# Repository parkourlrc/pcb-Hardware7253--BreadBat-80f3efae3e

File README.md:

# BreadBat
A breadboard power supply that can operate from USB power or battery power with a
selectable output voltage of 3.3V or 5V.
The device also includes a 1.5A battery charger and battery fuel gauge.

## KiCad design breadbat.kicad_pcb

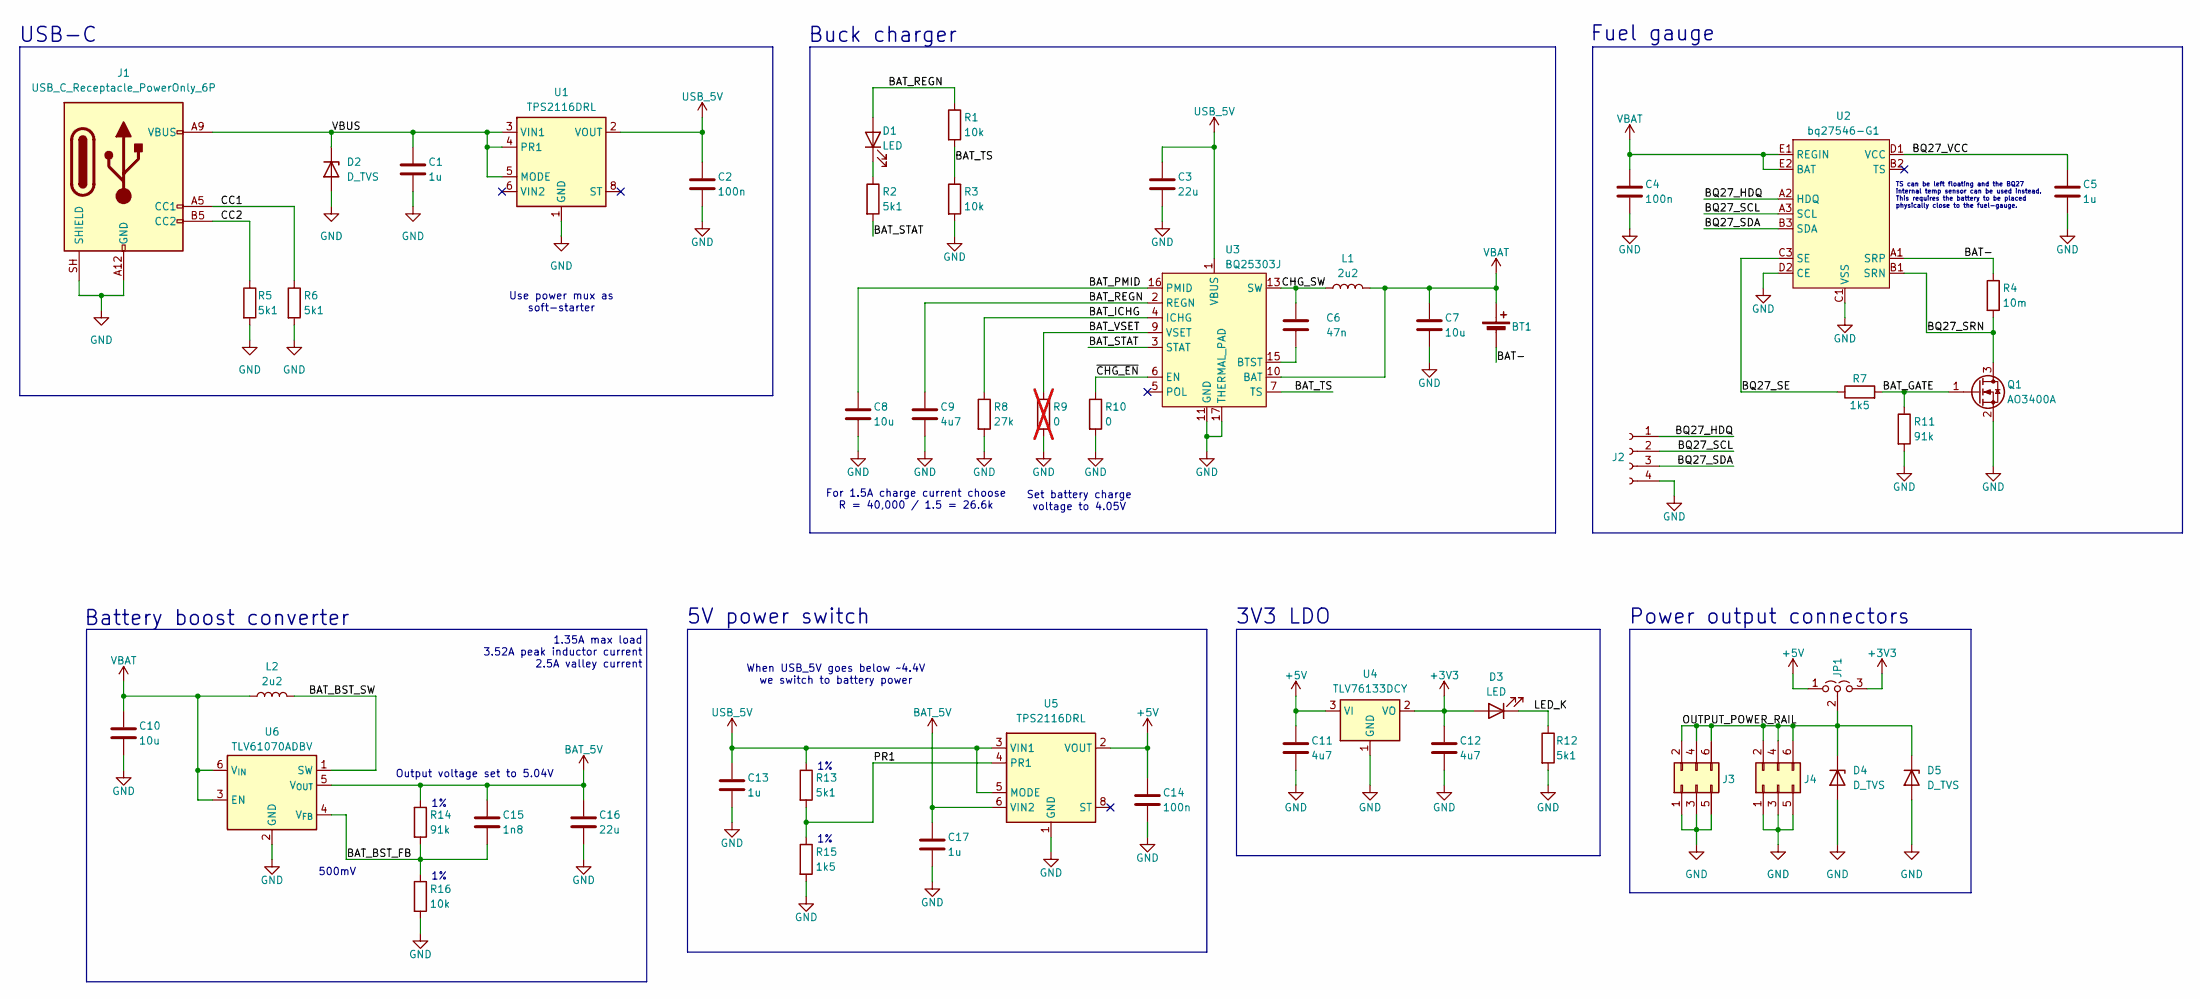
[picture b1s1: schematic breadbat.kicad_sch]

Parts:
BT1: Battery_Cell; JST_PH_B2B-PH-K_1x02_P2.00mm_Vertical_Pin_Swap
C1, C5, C13, C17: 1u; C_0402_1005Metric; LCSC part C29266
C2, C4, C14: 100n; C_0402_1005Metric; LCSC part C1525
C3, C16: 22u; C_0603_1608Metric; LCSC part C7432770
C6: 47n; C_0402_1005Metric; LCSC part C1622
C7, C8, C10: 10u; C_0603_1608Metric; LCSC part C962136
C9, C11, C12: 4u7; C_0603_1608Metric; LCSC part C1705
C15: 1n8; C_0402_1005Metric; LCSC part C107024
D1, D3: LED; LED_0603_1608Metric; LCSC part C2286
D2, D4, D5: D_TVS; D_SOD-323_HandSoldering; Part Number WPE0731D3; LCSC part C5143684
J1: USB_C_Receptacle_PowerOnly_6P; USB_C_Receptacle_HRO_TYPE-C-31-M-17; Part Number YTC-TC6S-231; LCSC part C2927302
J2: Conn_01x04_Socket; PinHeader_1x04_P2.54mm_Vertical
J3, J4: Conn_02x03_Odd_Even; PinHeader_2x03_P2.54mm_Vertical; Part Number PZ254V-12-6P; LCSC part C492420
JP1: Jumper_3_Open; PinHeader_1x03_P2.54mm_Vertical
L1, L2: 2u2; SMD,4.8x4.2mm; LCSC part C54431770
Q1: AO3400A; SOT-23; LCSC part C347475
R1, R3, R16: 10k; R_0402_1005Metric; LCSC part C25744
R2, R12, R13: 5k1; R_0402_1005Metric; LCSC part C25905
R4: 10m; R_1206_3216Metric; LCSC part C46961737
R5, R6: 5k1; R_0402_1005Metric; Part Number 0603WAF5101T5E; LCSC part C25905
R7, R15: 1k5; R_0402_1005Metric; LCSC part C25867
R8: 27k; R_0402_1005Metric; LCSC part C2933084
R9: 0; R_0402_1005Metric; LCSC part C106231; not fitted
R10: 0; R_0402_1005Metric; LCSC part C106231
R11, R14: 91k; R_0402_1005Metric; LCSC part C2909393
U1, U5: TPS2116DRL; SOT-583-8; LCSC part C3235557
U2: bq27546-G1; Texas_DSBGA-15_2.61x1.96mm_Layout5x3_P0.5mm; LCSC part C528629
U3: BQ25303J; WQFN-16-1EP_3x3mm_P0.5mm_EP1.68x1.68mm; LCSC part C2842775
U4: TLV76133DCY; SOT-223-3_TabPin2; LCSC part C7527500
U6: TLV61070ADBV; SOT-23-6; LCSC part C6881375

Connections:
+3V3: C12.1, D3.2 (A), JP1.3 (B), U4.2 (VO)
+5V: C11.1, C14.1, JP1.1 (A), U4.3 (VI), U5.2 (VOUT), U5.7 (VOUT)
/BAT-: BT1.2 (-), R4.1, U2.A1 (SRP)
/BAT_BST_FB: C15.2, R14.2, R16.1, U6.4 (V_{FB})
/BAT_BST_SW: L2.2, U6.1 (SW)
/BAT_GATE: Q1.1 (G), R7.2, R11.1
/BAT_ICHG: R8.1, U3.4 (ICHG)
/BAT_PMID: C8.1, U3.16 (PMID)
/BAT_REGN: C9.1, D1.2 (A), R1.1, U3.2 (REGN)
/BAT_STAT: R2.2, U3.3 (STAT)
/BAT_TS: R1.2, R3.1, U3.7 (TS)
/BAT_VSET: R9.1, U3.9 (VSET)
/BQ27_HDQ: J2.1, U2.A2 (HDQ)
/BQ27_SCL: J2.2, U2.A3 (SCL)
/BQ27_SDA: J2.3, U2.B3 (SDA)
/BQ27_SE: R7.1, U2.C3 (SE)
/BQ27_SRN: Q1.3 (D), R4.2, U2.B1 (SRN)
/BQ27_VCC: C5.1, U2.D1 (VCC)
/CC1: J1.A5 (CC1), R6.1
/CC2: J1.B5 (CC2), R5.1
/CHG_SW: C6.1, L1.1, U3.13 (SW), U3.14 (SW)
/LED_K: D3.1 (K), R12.1
/OUTPUT_POWER_RAIL: D4.1 (K), D5.1 (K), J3.2, J3.4, J3.6, J4.2, J4.4, J4.6, JP1.2 (C)
/PR1: R13.2, R15.1, U5.4 (PR1)
/VBUS: C1.1, D2.1 (K), J1.A9 (VBUS), J1.B9 (VBUS), U1.3 (VIN1), U1.4 (PR1), U1.5 (MODE)
/~CHG_EN: R10.1, U3.6 (EN)
BAT_5V: C15.1, C16.1, C17.1, R14.1, U5.6 (VIN2), U6.5 (V_{OUT})
GND: C1.2, C2.2, C3.2, C4.2, C5.2, C7.2, C8.2, C9.2, C10.2, C11.2, C12.2, C13.2, C14.2, C16.2, C17.2, D2.2 (A), D4.2 (A), D5.2 (A), J1.A12 (GND), J1.B12 (GND), J1.SH (SHIELD), J2.4, J3.1, J3.3, J3.5, J4.1, J4.3, J4.5, Q1.2 (S), R3.2, R5.2, R6.2, R8.2, R9.2, R10.2, R11.2, R12.2, R15.2, R16.2, U1.1 (GND), U2.C1 (VSS), U2.C2 (VSS), U2.D2 (CE), U3.11 (GND), U3.12 (GND), U3.17 (THERMAL_PAD), U4.1 (GND), U5.1 (GND), U6.2 (GND)
unnamed: D1.1 (K), R2.1
unnamed: C6.2, U3.15 (BTST)
USB_5V: C2.1, C3.1, C13.1, R13.1, U1.2 (VOUT), U1.7 (VOUT), U3.1 (VBUS), U5.3 (VIN1), U5.5 (MODE)
VBAT: BT1.1 (+), C4.1, C7.1, C10.1, L1.2, L2.1, U2.E1 (REGIN), U2.E2 (BAT), U3.10 (BAT), U6.3 (EN), U6.6 (V_{IN})

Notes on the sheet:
Power output connectors
For 1.5A charge current choose R = 40,000 / 1.5 = 26.6k
1.35A max load 3.52A peak inductor current 2.5A valley current
Fuel gauge
500mV
TS can be left floating and the BQ27 internal temp sensor can be used instead. This requires the battery to be placed physically close to the fuel-gauge.
Buck charger
Battery boost converter
Output voltage set to 5.04V
When USB_5V goes below ~4.4V we switch to battery power
Set battery charge voltage to 4.05V
Use power mux as soft-starter
3V3 LDO
5V power switch
USB-C

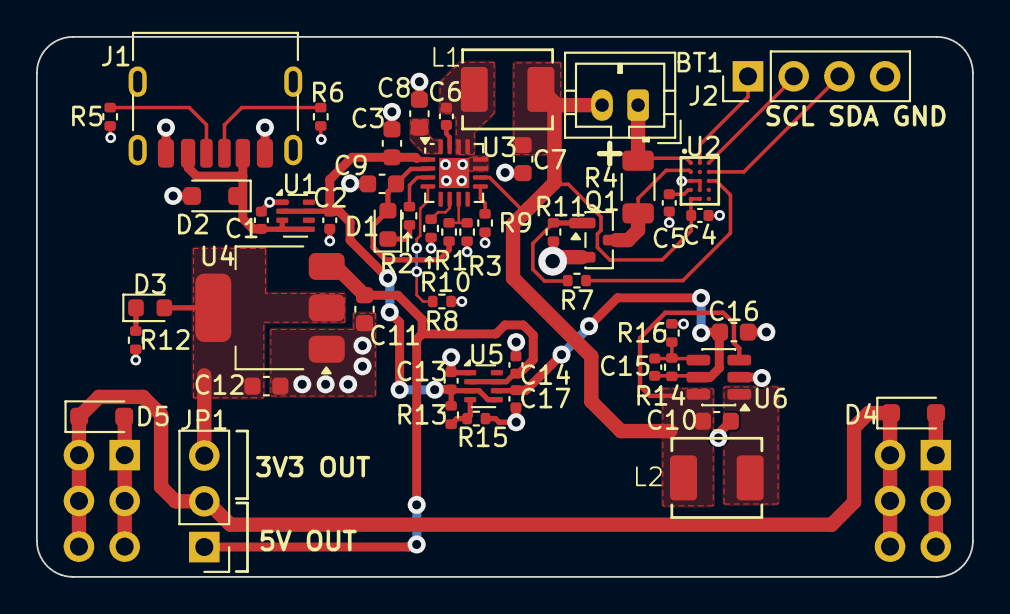
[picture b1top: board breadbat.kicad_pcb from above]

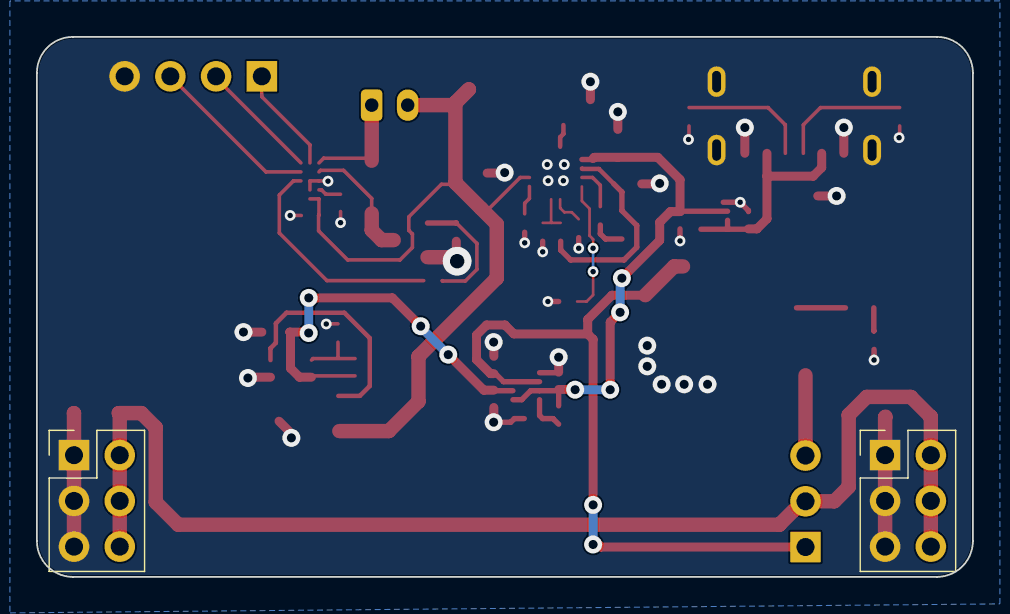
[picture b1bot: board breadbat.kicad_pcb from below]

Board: 2 copper layers, 52.0 x 30.0 mm, 53 parts (2 on the bottom side), 32 nets.
